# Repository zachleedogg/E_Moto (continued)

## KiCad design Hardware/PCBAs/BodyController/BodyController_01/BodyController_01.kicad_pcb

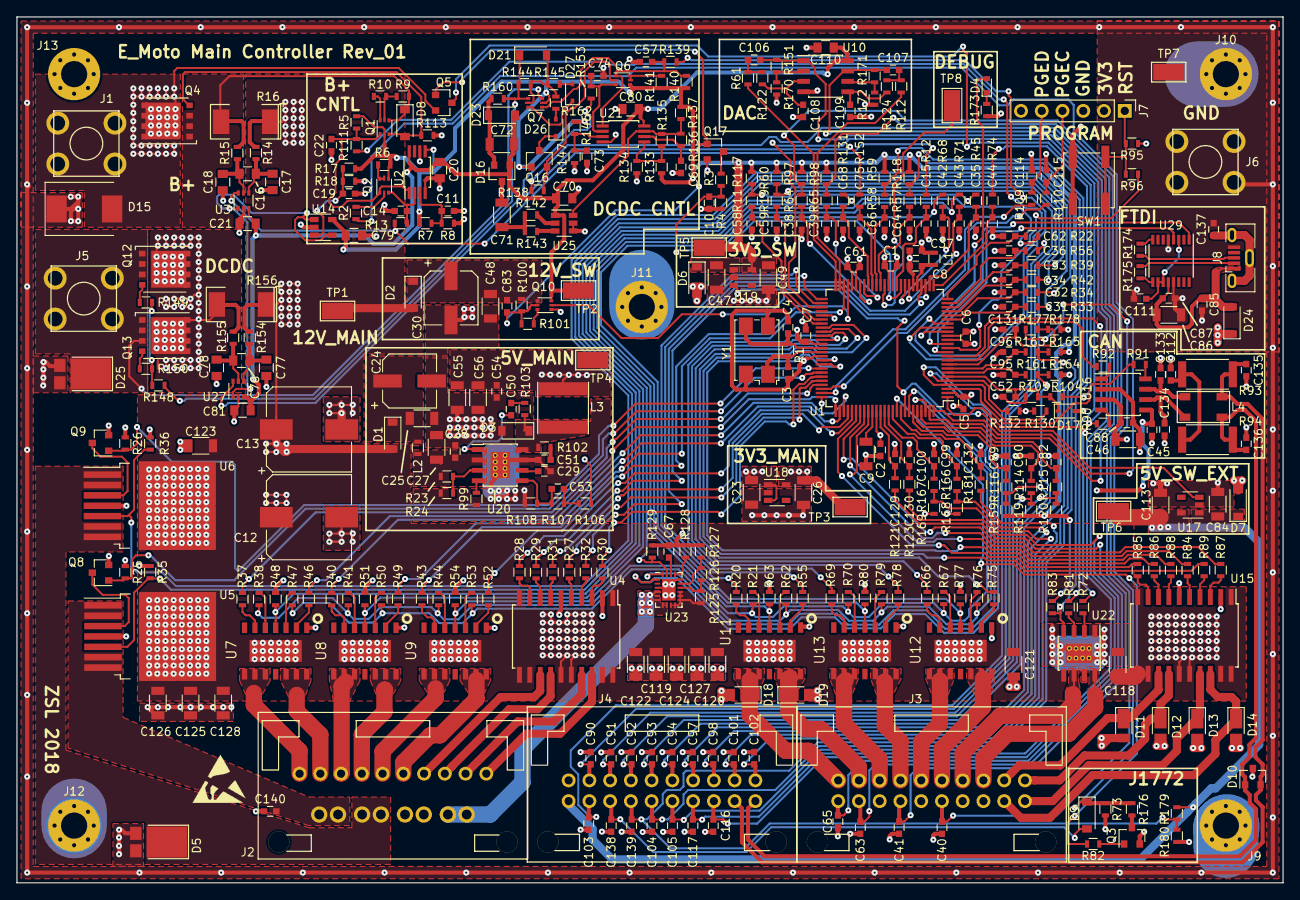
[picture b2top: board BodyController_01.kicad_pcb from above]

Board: 4 copper layers, 155.0 x 106.0 mm, 415 parts (0 on the bottom side), 284 nets.

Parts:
C1, C2, C5, C6, C7, C8, C37, C50, C61, C83, C87, C111: 100nF; C_0603
C3, C4, C53, C133, C134, C135, C136: 18pF; C_0603
C9, C26, C46, C49, C55, C56, C113, C118, C119, C120, C121, C122, C123, C124, C125, C126, C127, C128: 10uF; C_1206
C10, C11, C15, C19, C28, C29, C31, C32, C33, C34, C35, C36, C38, C39, C40, C41, C42, C43, C44, C45, C51, C52, C54, C58, C59, C60, C62, C63, C64, C65, C66, C67, C68, C73, C75, C82, C85, C88, C89, C90, C91, C92, C93, C94, C95, C96, C97, C98, C99, C100, C101, C102, C103, C104, C105, C106, C107, C108, C109, C112, C114, C115, C116, C117, C129, C130, C131, C132, C137, C138, C139, C140: 10nF; C_0603
C12, C13: 470uF; CP_Elec_10x10
C14, C22, C57, C69, C74: 1nF; C_0603
C16, C17, C18, C20, C21, C70, C76, C77, C78, C79, C80, C81, C110: 1uF; C_0805
C23, C25, C27, C47, C48, C71, C72, C84, C86: 4u7; C_1206
C24, C30: 47uF; CP_Elec_6.3x7.7
D1, D2, D3, D6, D7, D9, D24: D_Schottky; D_SOD-123
D4: D_LED; D_0603
D5, D25: D; SOT1289
D8, D21, D23: D_Zener_15V; D_SOD-123
D10: D_Schottky_x2_ACom_AKK; D_SOT-23_ANK
D11, D12, D13, D14, D18, D19: D; D_PowerDI-123
D15: D_TVS; D_SMC
D16: D_Schottky_x2_Serial_AKC; SOT-23
D17, D26, D27: D_Schottky; D_SOD-323
J1, J5, J6: 7796
J2: Conn_01x14; 34772-0140
J3, J4: Conn_02x10_Top_Bottom; 34690-0200
J7: CONN_01X06; Pin_Header_Straight_1x06_Pitch2.54mm
J8: USB_OTG; USB_Micro-B_Vertical_Molex-105133-0001
J9, J10, J11, J12, J13: Conn_01x01; MountingHole_3.2mm_M3_Pad_Via
L1, L2: Ferrite_Bead; L_0603
L3: 10uH; Inductor_Taiyo-Yuden_NR-60xx
L4: EMI_Filter_CommonMode; ACT45B
NT1, NT2, NT3, NT4: Net_Tie-0.5mm
Q1, Q2, Q6, Q7, Q10: NX1029X,115; SOT-666
Q3, Q8, Q9, Q16: 2N7002; SOT-23
Q4: SQJ423EP-T1_GE3; TDSON-8-1
Q5, Q17: Q_PMOS_GSD; SOT-23
Q12, Q13: BUK7J1R4-40HX; TDSON-8-1
R1: 1M; R_0603
R2, R20, R21, R27, R28, R30, R31, R37, R38, R40, R41, R43, R44, R46, R47, R49, R50, R52, R53, R55, R62, R66, R67, R69, R70, R72, R75, R76, R78, R79, R81, R82, R84, R85, R87, R88, R90, R91, R92, R109, R110, R138, R173: 100R; R_0603
R3, R104, R127: 34k; R_0603
R4, R35, R36, R48, R51, R54, R63, R77, R80, R83, R105, R160: 4k7; R_0603
R5, R6, R7, R10, R11, R12, R13, R17, R18, R19, R22, R29, R32, R39, R42, R45, R56, R57, R58, R64, R65, R68, R71, R74, R86, R89, R95, R96, R97, R98, R101, R113, R114, R115, R116, R121, R123, R129, R131, R137, R140, R141, R145, R146, R151, R152, R153, R161, R162, R163, R166, R167, R171, R181: 10k; R_0603
R8, R9, R25, R26, R59, R60, R100, R111, R117, R118, R119, R120, R126, R130, R132, R133, R134, R135, R136, R139, R144, R147, R159, R164, R165, R168, R169, R178: 100k; R_0603
R14, R15, R102, R103, R142, R143, R148, R149, R150, R154, R155: 3R0; R_0603
R16: R0005; SMD-2512_Pol
R23, R125, R177: 560k; R_0603
R24, R61, R108, R112, R122, R124: 150k; R_0603
R33, R34: 10K; R_0603
R73: 2k74; R_0603
R93, R94: 60R; R_2512
R99: 49k9; R_0603
R106, R174, R175: 22R; R_0603
R107: 845k; R_0603
R128, R170, R172: 22k; R_0603
R156: R0003; SMD-2512_Pol
R176: 1k3; R_0603
R179, R180: 330R; R_0603
SW1: PTS645SM43SMTR92 LFS; SW_SPST_EVQP0
TP1, TP2, TP3, TP4, TP5, TP6, TP7, TP8: TEST_1P; Test_Point_Keystone_5019_Minature
U1: PIC33EPxxxMU810; TQFP-100_14x14mm_Pitch0.5mm
U2, U21: LM2903QDRQ1; TSSOP-8_3x4.4mm_Pitch0.65mm
U3, U27: INA21x; SOT-363_SC-70-6
U4, U15: BTS716G; SOIC-20W_7.5x12.8mm_Pitch1.27mm
U5, U6: BTS500801TMAATMA1; TO-220-7Lead_TabPin8
U7, U8, U9, U11, U12, U13: BTS50202EKAXUMA2; PG_DSO_14_40_EP
U10: LM2904AVQDRQ1; SOIC-8_3.9x4.9mm_Pitch1.27mm
U14: OPA320-Q1; SOT-23-5
U16: TCAN1051GVDRQ1; SOIC-8_3.9x4.9mm_Pitch1.27mm
U17: TPS70950QDBVRQ1; SOT-23-5
U18, U19: TPS70933QDBVRQ1; SOT-23-5
U20: LMR140x0; HTSOP-8-1EP_3.9x4.9mm_Pitch1.27mm_ThermalVias
U22: DRV8872DDARQ1; HTSOP-8-1EP_3.9x4.9mm_Pitch1.27mm_ThermalVias
U23: tps25940-q1; QFN-20-1EP_3x4mm_Pitch0.5mm
U25: UCC27511A-Q1; SOT-23-6
U29: FT230X; SSOP-16_3.9x4.9mm_Pitch0.635mm
Y1: 8MHz; Crystal_SMD_7050-4pin_7.0x5.0mm

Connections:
1V65_REF: U3.1, U14.1, U14.4, U27.1
12P_MONITOR_AI: C52.1, D17.1, R104.2, R105.1, U1.6
12V_MONITOR_AI: C10.1, R3.2, R4.1, U1.34
+3.3VA: C8.1, L1.1, U1.30
+3.3VP: C49.1, C79.2, Q1.2, Q2.4, Q6.4, Q7.2, Q16.1, R5.1, R6.1, R7.1, R17.1, R59.1, R60.1, R83.1, R97.2, R98.2, R117.1, R118.1, R119.1, R120.1, R133.1, R137.1, R140.1, R141.1, R146.1, R159.1, R164.1, R165.1, TP5.1, U2.5, U14.5, U19.5
+3V3: C1.1, C2.1, C5.1, C6.1, C7.1, C26.1, C37.1, C45.1, C61.1, J7.2, L1.2, R95.1, R130.1, R132.1, R168.1, R169.1, TP3.1, U1.2, U1.16, U1.37, U1.46, U1.55, U1.62, U1.86, U16.5, U18.5
+5V: C23.1, C46.1, C54.1, C55.1, C56.1, C88.1, D24.1, L3.2, R106.1, TP4.1, U16.3, U18.1, U18.3
+5VP: C113.1, J4.11, R179.1, TP6.1, U17.5
+12P: C20.2, C21.2, C70.2, C72.2, C80.2, C81.2, C110.1, D16.1, D23.2, Q10.3, TP2.1, U2.8, U3.3, U10.8, U21.8, U25.1, U27.3
+12V: C12.1, C13.1, C118.1, C119.1, C120.1, C121.1, C122.1, C123.1, C124.1, C125.1, C126.1, C127.1, C128.1, D1.2, D2.2, D6.2, D7.2, NT2.1, NT4.1, Q17.2, R16.1, R125.2, R156.1, TP1.1, U4.1, U4.10, U4.11, U4.12, U4.15, U4.16, U4.19, U4.20, U5.4, U5.8, U6.4, U6.8, U7.TAB, U8.TAB, U9.TAB, U11.TAB, U12.TAB, U13.TAB, U15.1, U15.10, U15.11, U15.12, U15.15, U15.16, U15.19, U15.20, U22.5, U23.9, U23.10, U23.11, U23.12, U23.13
+BATT: D15.2, J1.1, Q4.5, Q5.2
/TopLevel/Communication/CAN_FILT_N: C134.2, L4.3, U16.6
/TopLevel/Communication/CAN_FILT_P: C133.2, L4.1, U16.7
/TopLevel/DCDC/ChargePump: C72.1, D16.2, D23.1, R160.1
/TopLevel/DCDC/DCDC_SHUNT: NT3.1, Q12.5, Q13.5, R156.2
/TopLevel/PowerInput/BATT_SHUNT: D8.1, NT1.1, Q1.4, Q4.1, Q4.2, Q4.3, R9.1, R16.2
/TopLevel/PowerRails/buck_bt: C50.2, U20.1
/TopLevel/PowerRails/buck_fb: C53.2, R107.2, R108.1, U20.5
/TopLevel/PowerRails/buck_freq: R99.1, U20.4
/TopLevel/PowerRails/buck_holdup: C24.1, C25.1, D1.1, L2.2
/TopLevel/PowerRails/buck_input: C27.1, C28.1, L2.1, R23.1, U20.2
/TopLevel/PowerRails/buck_ss: C29.1, U20.6
/TopLevel/PowerRails/buck_sw: D3.1, L3.1, R102.2, R103.1, U20.8
/TopLevel/PowerRails/buck_uvlo: R23.2, R24.1, U20.3
AUX_PORT_EN: Q8.1, R25.1, U1.69
AUX_PORT_ISENSE_AI: C31.1, R33.2, U1.20
AUX_PORT_OUT: C140.1, J2.11, U5.1, U5.2, U5.6, U5.7
BATTERY_CONTACTOR_EN: R84.2, U1.83
BATTERY_CONTACTOR_OUT: D13.1, J3.20, U15.17
BATT_EN: R2.2, U1.100
BATT_ISENSE_AI: C15.1, R12.2, U1.35
BATT_~FAULT: R111.2, U1.19
BMS_CONTROLLER_EN: R75.2, U1.58
BMS_CONTROLLER_OUT: J3.6, U12.12, U12.13, U12.14
BRAKE_LIGHT_EN: R37.2, U1.72
BRAKE_LIGHT_OUT: J2.1, U7.8, U7.9, U7.10
BRAKE_SWITCH_1: C104.1, J4.15, R57.1, R118.2
BRAKE_SWITCH_1_IN: C64.1, R57.2, U1.39
BRAKE_SWITCH_2: C105.1, J4.16, R58.1, R59.2
BRAKE_SWITCH_2_IN: C66.1, R58.2, U1.40
BRIGHTS_SWITCH: C92.1, J4.4, R114.1, R119.2
BRIGHTS_SWITCH_IN: C60.1, R114.2, U1.96
CAN_N: C136.2, D10.2, J4.20, L4.4, R94.1
CAN_P: C135.2, D10.3, J4.19, L4.2, R93.2
CAN_RX: R90.2, U1.11
CAN_SLEEP: R91.2, U1.3
CAN_TX: R92.2, U1.10
CHARGER_CONTACTOR_EN: R85.2, U1.81
CHARGER_CONTACTOR_OUT: D11.1, J3.9, U15.13
CHARGE_CONTROLLER_EN: R69.2, U1.61
CHARGE_CONTROLLER_OUT: J3.3, U13.8, U13.9, U13.10
CHARGE_PORT_RELEASE_EN: R81.2, U1.53
CHARGE_PORT_RELEASE_OUT: J3.8, U22.8
CONTACT_1_2_STATUS: R89.2, U1.66
CONTACT_3_4_STATUS: R86.2, U1.67
DAC_OUT_1: C106.1, C117.1, J4.17, R151.2, U10.1
DAC_OUT_2: C107.1, C116.1, J4.18, R171.2, U10.7
DAC_PWM_1: R61.1, U1.50
DAC_PWM_2: R112.1, U1.49
DCDC: D25.1, J5.1, Q7.3, Q12.1, Q12.2, Q12.3, Q13.1, Q13.2, Q13.3
DCDC_CONTACTOR_EN: R87.2, U1.82
DCDC_CONTACTOR_OUT: D14.1, J3.19, U15.18
DCDC_EN: R138.2, U1.99
DCDC_ISENSE_AI: C75.1, R152.2, U1.41
DCDC_~FAULT: R139.2, U1.18
DEBUG_LED: D4.2, U1.17
DEBUG_PIN: TP8.1, U1.38
DIAG_EN: R47.2, R50.2, R53.2, R62.2, R76.2, R79.2, U1.94
DIAG_SELECT: R21.2, R38.2, R41.2, R44.2, R67.2, R70.2, U1.98
DIVIDER_EN: C83.2, Q5.1, Q10.5, Q17.1, R100.2, R101.1
ECU_1_ISENSE_AI: C42.1, R68.2, U1.33
ECU_2_ISENSE_AI: C43.1, R71.2, U1.32
FAN_1_EN: R55.2, U1.51
FAN_1_OUT: D19.1, J3.2, U11.12, U11.13, U11.14
FAN_ISENSE_AI: C62.1, R22.2, U1.25
FAN_SPEED_1_OUT: C63.1, J3.12, R121.1
FAN_SPEED_1_PWM: C129.1, R121.2, U1.87
GND: C1.2, C2.2, C3.2, C4.2, C5.2, C6.2, C7.2, C8.2, C9.2, C10.2, C11.2, C12.2, C13.2, C14.1, C15.2, C17.2, C18.2, C19.2, C20.1, C21.1, C22.1, C23.2, C24.2, C25.2, C26.2, C27.2, C28.2, C29.2, C30.2, C31.2, C32.2, C33.2, C34.2, C35.2, C36.2, C37.2, C38.2, C39.2, C40.2, C41.2, C42.2, C43.2, C44.2, C45.2, C46.2, C47.2, C48.2, C49.2, C51.1, C52.2, C54.2, C55.2, C56.2, C57.1, C58.2, C59.2, C60.2, C61.2, C62.2, C63.2, C64.2, C65.2, C66.2, C67.2, C68.2, C69.2, C70.1, C73.2, C74.1, C75.2, C77.2, C78.2, C79.1, C80.1, C81.1, C82.2, C84.2, C85.2, C86.2, C87.2, C88.2, C89.2, C90.2, C91.2, C92.2, C93.2, C94.2, C95.2, C96.2, C97.2, C98.2, C99.2, C100.2, C101.2, C102.2, C103.2, C104.2, C105.2, C108.2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
HEADLIGHT_HI_EN: R49.2, U1.77
HEADLIGHT_HI_OUT: J2.4, U8.12, U8.13, U8.14
HEADLIGHT_ISENSE_AI: C34.1, R42.2, U1.22
HEADLIGHT_LO_EN: R40.2, U1.78
HEADLIGHT_LO_OUT: J2.3, U8.8, U8.9, U8.10
HEATED_GRIPS_EN: R52.2, U1.47
HEATED_GRIPS_OUT: J2.6, U9.12, U9.13, U9.14
HEATED_SEAT_EN: R43.2, U1.48
HEATED_SEAT_OUT: J2.5, U9.8, U9.9, U9.10
HEATER_ISENSE_AI: C35.1, R45.2, U1.27
HORN_EN: Q9.1, R26.1, U1.68
HORN_ISENSE_AI: C32.1, R34.2, U1.21
HORN_OUT: D5.1, J2.12, U6.1, U6.2, U6.6, U6.7
HORN_SWITCH: C93.1, J4.5, R115.1, R120.2
HORN_SWITCH_IN: C82.1, R115.2, U1.97
IC_CONTROLLER_ISENSE_AI: C68.1, R131.2, U1.42
IC_CONTROLLER_OUT: J2.14, U23.4, U23.5, U23.6, U23.7, U23.8
IC_CONTROLLER_SLEEP: R130.2, U1.4, U23.1
IC_CONTROLLER_~FLT: R132.2, U1.5, U23.20
IGNITION_SWITCH_IN: C99.1, R166.2, U1.90
INGITION_SWITCH: C101.1, J4.9, R166.1, R168.2
J1772_CONTROLLER_EN: R66.2, U1.59
J1772_CONTROLLER_OUT: J3.5, U12.8, U12.9, U12.10
KICKSTAND_SWITCH: C94.1, J4.6, R116.1, R159.2
KICKSTAND_SWITCH_IN: C89.1, R116.2, U1.95
KILL_SWITCH: C102.1, J4.10, R167.1, R169.2
KILL_SWITCH_IN: C100.1, R167.2, U1.89
LOCK_ISENSE_AI: C44.1, R74.2, U1.26
MOTOR_CONTROLLER_EN: R78.2, U1.60
MOTOR_CONTROLLER_OUT: J3.4, U13.12, U13.13, U13.14
unnamed: C3.1, R1.1, U1.64, Y1.1
unnamed: C4.1, R1.2, U1.63, Y1.3
unnamed: C9.1, U1.85
unnamed: C11.1, R7.2, R8.1, U2.3
unnamed: C14.2, Q2.3, R13.2, U2.2
unnamed: C16.1, C18.1, R15.2, U3.5
unnamed: C16.2, C17.1, R14.2, U3.4
unnamed: C19.1, R17.2, R18.1, U14.3
unnamed: C22.2, Q1.1, Q2.1, R5.2, R111.1, U2.1
unnamed: C30.1, C48.1, C83.1, D2.1, Q10.4, R100.1
unnamed: C47.1, D6.1, U19.1
unnamed: C50.1, R103.2
unnamed: C51.2, R102.1
unnamed: C53.1, R106.2, R107.1
unnamed: C57.2, Q6.1, Q7.1, R139.1, R140.2, U21.1
unnamed: C67.1, U23.18
unnamed: C69.1, R136.2, U21.6
unnamed: C71.1, D16.3
unnamed: C71.2, R142.1, R143.1
unnamed: C73.1, R146.2, R147.1, U21.3
unnamed: C74.2, Q6.3, R153.2, U21.2
unnamed: C76.1, C78.1, R155.2, U27.5
unnamed: C76.2, C77.1, R154.2, U27.4
unnamed: C84.1, D7.1, U17.1
unnamed: C106.2, R61.2, R122.1
unnamed: C107.2, R112.2, R124.1
unnamed: C108.1, R122.2, U10.3
unnamed: C109.1, R124.2, U10.5
unnamed: C111.1, U29.3, U29.10, U29.11
unnamed: C112.1, R93.1, R94.2
unnamed: C114.1, J7.5, R109.1
unnamed: C115.1, J7.4, R110.1
unnamed: C137.1, J8.6
unnamed: D4.1, R173.2
unnamed: D8.2, Q1.3, Q4.4, R113.1
unnamed: D9.1, R73.1, R176.1, R177.1
unnamed: D21.1, Q7.4, R144.1, R148.1, R160.2
unnamed: D21.2, Q7.5, R144.2, R145.1, R162.1
unnamed: D26.1, Q16.3
unnamed: D26.2, R162.2
unnamed: D27.1, Q7.6
unnamed: D27.2, R145.2
unnamed: NT1.2, R15.1
unnamed: NT2.2, R14.1
unnamed: NT3.2, R155.1
unnamed: NT4.2, R154.1
unnamed: Q1.5, R9.2, R10.1
unnamed: Q1.6, R10.2
unnamed: Q2.2, R2.1
unnamed: Q2.5, Q2.6, R6.2
unnamed: Q3.1, R82.1
unnamed: Q3.3, R176.2
unnamed: Q5.3, R104.1
unnamed: Q6.5, Q6.6, R141.2
unnamed: Q8.3, U5.3
unnamed: Q9.3, U6.3
unnamed: Q10.6, R101.2
unnamed: Q12.4, R149.2
unnamed: Q13.4, R150.2
unnamed: Q6.2, Q16.2, R138.1
unnamed: Q17.3, R3.1
unnamed: R12.1, R13.1, U3.6
unnamed: R20.1, U11.6
unnamed: R21.1, U11.5
unnamed: R22.1, R63.2, U11.4
unnamed: R27.1, U4.5
unnamed: R28.1, U4.9
unnamed: R29.1, U4.8
unnamed: R30.1, U4.3
unnamed: R31.1, U4.7
unnamed: R32.1, U4.4
unnamed: R33.1, R35.2, U5.5
unnamed: R34.1, R36.2, U6.5
unnamed: R37.1, U7.6
unnamed: R38.1, U7.5
unnamed: R39.1, R48.2, U7.4
unnamed: R40.1, U8.6
unnamed: R41.1, U8.5
unnamed: R42.1, R51.2, U8.4
unnamed: R43.1, U9.6
unnamed: R44.1, U9.5
unnamed: R45.1, R54.2, U9.4
unnamed: R46.1, U7.2
unnamed: R47.1, U7.3
unnamed: R49.1, U8.2
unnamed: R50.1, U8.3
unnamed: R52.1, U9.2
unnamed: R53.1, U9.3
unnamed: R55.1, U11.2
unnamed: R62.1, U11.3
unnamed: R66.1, U12.6
unnamed: R67.1, U12.5
unnamed: R68.1, R77.2, U12.4
unnamed: R69.1, U13.6
unnamed: R70.1, U13.5
unnamed: R71.1, R80.2, U13.4
unnamed: R72.1, U22.2
unnamed: R74.1, R83.2, U22.4
unnamed: R75.1, U12.2
unnamed: R76.1, U12.3
unnamed: R78.1, U13.2
unnamed: R79.1, U13.3
unnamed: R81.1, U22.3
unnamed: R84.1, U15.5
unnamed: R85.1, U15.9
unnamed: R86.1, U15.8
unnamed: R87.1, U15.3
unnamed: R88.1, U15.7
unnamed: R89.1, U15.4
unnamed: R90.1, U16.4
unnamed: R91.1, U16.8
unnamed: R92.1, U16.1
unnamed: R96.1, U1.13
unnamed: R125.1, R126.2, U23.14
unnamed: R126.1, R127.2, U23.15
unnamed: R128.2, U23.17
unnamed: R129.2, R131.1, U23.19
unnamed: R133.2, R134.1, R135.2, U21.5
unnamed: R135.1, R136.1, R137.2, U21.7, U25.6
unnamed: R142.2, U25.2
unnamed: R143.2, U25.3
unnamed: R148.2, R149.1, R150.1
unnamed: R151.1, R170.2, U10.2
unnamed: R152.1, R153.1, U27.6
unnamed: R171.1, R172.2, U10.6
unnamed: R174.2, U29.8
unnamed: R175.2, U29.9
PGEC: R109.2, U1.74
PGED: R110.2, U1.73
PILOT: C138.1, D9.2, J4.13
PILOT_EN: R82.2, U1.91
PILOT_MONITOR_AI: C131.1, R177.2, R178.1, U1.9
PRECHARGE_RELAY_EN: R88.2, U1.84
PRECHARGE_RELAY_OUT: D12.1, J3.10, U15.14
PROXIMITY: C139.1, J4.14, R179.2, R180.1, R181.2
PROXIMITY_MONITOR_AI: C132.1, R181.1, U1.92
PUMP_1_EN: R20.2, U1.52
PUMP_1_OUT: D18.1, J3.1, U11.8, U11.9, U11.10
PUMP_SPEED_1_OUT: C65.1, J3.11, R123.1
PUMP_SPEED_1_PWM: C130.1, R123.2, U1.88
RADIATOR_INPUT_TEMP_AI: C39.1, R65.2, U1.43
RADIATOR_INPUT_TEMP_OUT: C41.1, J3.14, R65.1, R98.1
RADIATOR_OUTPUT_TEMP_AI: C38.1, R64.2, U1.44
RADIATOR_OUTPUT_TEMP_OUT: C40.1, J3.16, R64.1, R97.1
SPARE_SWITCH_1: C97.1, J4.7, R161.1, R164.2
SPARE_SWITCH_1_IN: C95.1, R161.2, U1.7
SPARE_SWITCH_2: C98.1, J4.8, R163.1, R165.2
SPARE_SWITCH_2_IN: C96.1, R163.2, U1.8
STEERING_COLUMN_LOCK_EN: R72.2, U1.1
STEERING_COLUMN_LOCK_OUT: J3.7, U22.6
SW_EN: Q10.2, U1.93, U17.3, U19.3
TAILLIGHT_EN: R46.2, U1.76
TAILLIGHT_ISENSE_AI: C33.1, R39.2, U1.23
TAILLIGHT_OUT: J2.2, U7.12, U7.13, U7.14
THROTTLE_SIGNAL: C103.1, J4.12, R56.1
THROTTLE_SIGNAL_MONITOR_AI: C36.1, R56.2, U1.24
TURN_LEFT_SWITCH: C90.1, J4.2, R11.1, R117.2
TURN_LEFT_SWITCH_IN: C58.1, R11.2, U1.57
TURN_RIGHT_SWITCH: C91.1, J4.3, R19.1, R60.2
TURN_RIGHT_SWITCH_IN: C59.1, R19.2, U1.56
TURN_SGINAL_FL_EN: R31.2, U1.79
TURN_SIGNAL_FL_OUT: J2.8, U4.14
TURN_SIGNAL_FR_EN: R30.2, U1.70
TURN_SIGNAL_FR_OUT: J2.10, U4.18
TURN_SIGNAL_L_STATUS: R29.2, U1.29
TURN_SIGNAL_RL_EN: R28.2, U1.80
TURN_SIGNAL_RL_OUT: J2.7, U4.13
TURN_SIGNAL_RR_EN: R27.2, U1.71
TURN_SIGNAL_RR_OUT: J2.9, U4.17
TURN_SIGNAL_R_STATUS: R32.2, U1.28
UART_RX: U1.14, U29.1
UART_TX: U1.12, U29.4
USB_5V: C85.1, C86.1, C87.1, D24.2, J8.1, U29.12
USB_D+: J8.3, R174.1
USB_D-: J8.2, R175.1
~RESET: J7.1, R95.2, R96.2, SW1.2

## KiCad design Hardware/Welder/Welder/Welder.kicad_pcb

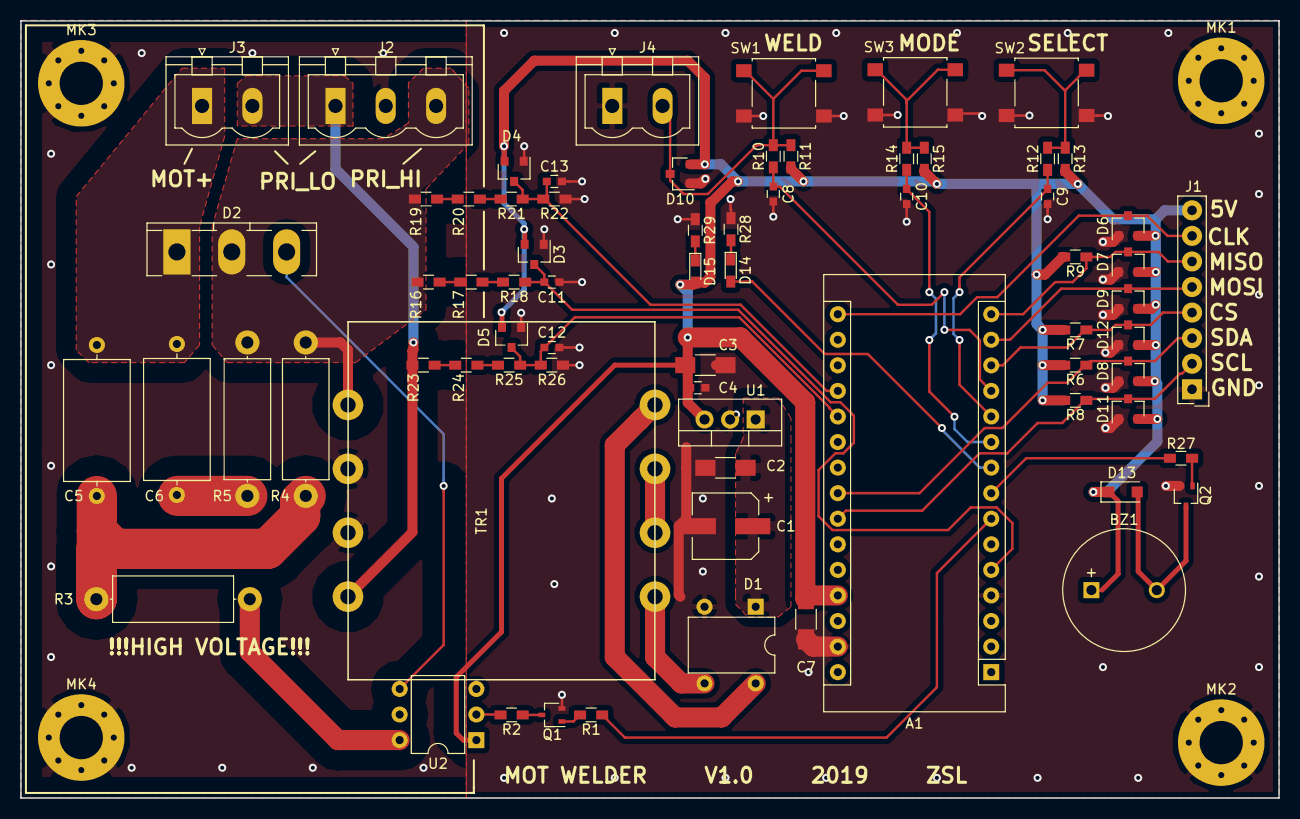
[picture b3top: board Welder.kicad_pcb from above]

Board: 2 copper layers, 125.0 x 77.2 mm, 75 parts (0 on the bottom side), 44 nets.

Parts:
A1: Arduino_Nano_v3.x; Arduino_Nano
BZ1: Buzzer; MagneticBuzzer_ProSignal_ABT-410-RC
C1: 47u; CP_Elec_6.3x7.7
C2, C3, C7: 10uF; C_1206_HandSoldering
C4, C8, C9, C10, C11, C12, C13: 10nF; C_0603
C5: 0.047uF; C_Axial_L12.0mm_D6.5mm_P15.00mm_Horizontal
C6: 0.1uF; C_Axial_L12.0mm_D6.5mm_P15.00mm_Horizontal
D1: D_Bridge_+-AA; Diode_Bridge_DIP-4_W7.62mm_P5.08mm
D2: Q_TRIAC_A1A2G; TO-280_Vertical
D3, D4, D5, D6, D7, D8, D9, D10, D11, D12: D_Schottky_x2_Serial_AKC; SOT-23
D13: D; D_SOD-123F
D14, D15: LED; LED_0603_HandSoldering
J1: Conn_01x08; SL-108-X-XX_1x08
J2: Screw_Terminal_01x03; PhoenixContact_MSTBVA-G_03x5.00mm_Vertical
J3, J4: Screw_Terminal_01x02; PhoenixContact_MSTBVA-G_02x5.00mm_Vertical
MK1, MK2, MK3, MK4: Mounting_Hole_PAD; MountingHole_4.3mm_M4_Pad_Via
Q1, Q2: Q_NMOS_GSD; SOT-323_SC-70
R1, R6, R7, R8, R9, R10, R11, R12, R13, R14, R15, R27: 10k; R_0603_HandSoldering
R2: 220R; R_0603_HandSoldering
R3: 360R; R_Axial_DIN0414_L11.9mm_D4.5mm_P15.24mm_Horizontal
R4: 470R; R_Axial_DIN0414_L11.9mm_D4.5mm_P15.24mm_Horizontal
R5: 39R; R_Axial_DIN0414_L11.9mm_D4.5mm_P15.24mm_Horizontal
R16, R17, R18, R19, R20, R21, R23, R24, R25: 165k; R_0603_HandSoldering
R22, R26: 14k7; R_0603_HandSoldering
R28, R29: 360R; R_0603_HandSoldering
SW1, SW2, SW3: SW_Push; SW_SPST_B3S-1000
TR1: TRANSF6; FS20-120-C2
U1: LM7805_TO220; TO-220-3_Vertical
U2: MOC3052M; DIP-6_W7.62mm

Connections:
+5V: A1.27, BZ1.1, C3.1, C4.1, C7.1, D3.2, D4.2, D5.2, D6.2, D7.2, D8.2, D9.2, D10.2, D11.2, D12.2, D13.1, D15.2, J1.8, R6.2, R7.2, R8.2, R9.2, R11.2, R13.2, R15.2, U1.3, U2.1
BUZZ_PWM: A1.8, R27.1
CLK: A1.16, D6.3, J1.7
CS: A1.13, D12.3, J1.4, R7.1
DEBUG_LED_EN: A1.9, D14.2
GND: A1.4, A1.29, C1.2, C2.2, C3.2, C4.2, C7.2, C8.2, C9.2, C10.2, C11.2, C12.2, C13.2, D1.2, D3.1, D4.1, D5.1, D6.1, D7.1, D8.1, D9.1, D10.1, D11.1, D12.1, J1.1, J2.2, J4.1, MK1.1, MK2.1, MK3.1, MK4.1, Q1.2, Q2.2, R22.1, R26.1, R28.1, R29.1, SW1.2, SW2.2, SW3.2, TR1.2, TR1.3, U1.2
MISO: A1.15, D7.3, J1.6, R9.1
MODE_BUTTON: A1.10, C10.1, R14.1
MOSI: A1.14, D9.3, J1.5
MOT_+: C5.2, C6.2, D2.1, J3.1
MOT_EN: A1.7, R1.1
unnamed: BZ1.2, D13.2, Q2.3
unnamed: C1.1, C2.1, D1.1, U1.1
unnamed: C5.1, R3.1, R4.2
unnamed: C6.1, R5.2
unnamed: D1.3, TR1.8
unnamed: D1.4, TR1.5
unnamed: D2.3, U2.4
unnamed: D14.1, R28.2
unnamed: D15.1, R29.2
unnamed: Q1.1, R1.2
unnamed: Q1.3, R2.1
unnamed: Q2.1, R27.2
unnamed: R2.2, U2.2
unnamed: R3.2, U2.6
unnamed: R12.2, R13.1, SW2.1
unnamed: R14.2, R15.1, SW3.1
unnamed: R16.1, R17.2
unnamed: R17.1, R18.2
unnamed: R19.1, R20.2
unnamed: R20.1, R21.2
unnamed: R23.1, R24.2
unnamed: R24.1, R25.2
unnamed: TR1.6, TR1.7
PRIMARY_A_AI: A1.19, C13.1, D4.3, R21.1, R22.2
PRIMARY_B_AI: A1.20, C12.1, D5.3, R25.1, R26.2
PRI_HI: D2.2, J2.3, R4.1, R5.1, R16.2, R19.2, TR1.1
PRI_LO: J2.1, J3.2, R23.2, TR1.4
SCL: A1.24, D11.3, J1.2, R8.1
SDA: A1.23, D8.3, J1.3, R6.1
SELECT_BUTTON: A1.11, C9.1, R12.1
WELD_BUTTON: A1.12, C8.1, R10.1
WELD_BUTTON_OUT: D10.3, J4.2, R10.2, R11.1, SW1.1
ZERO_CROSS: A1.5, C11.1, D3.3, R18.1

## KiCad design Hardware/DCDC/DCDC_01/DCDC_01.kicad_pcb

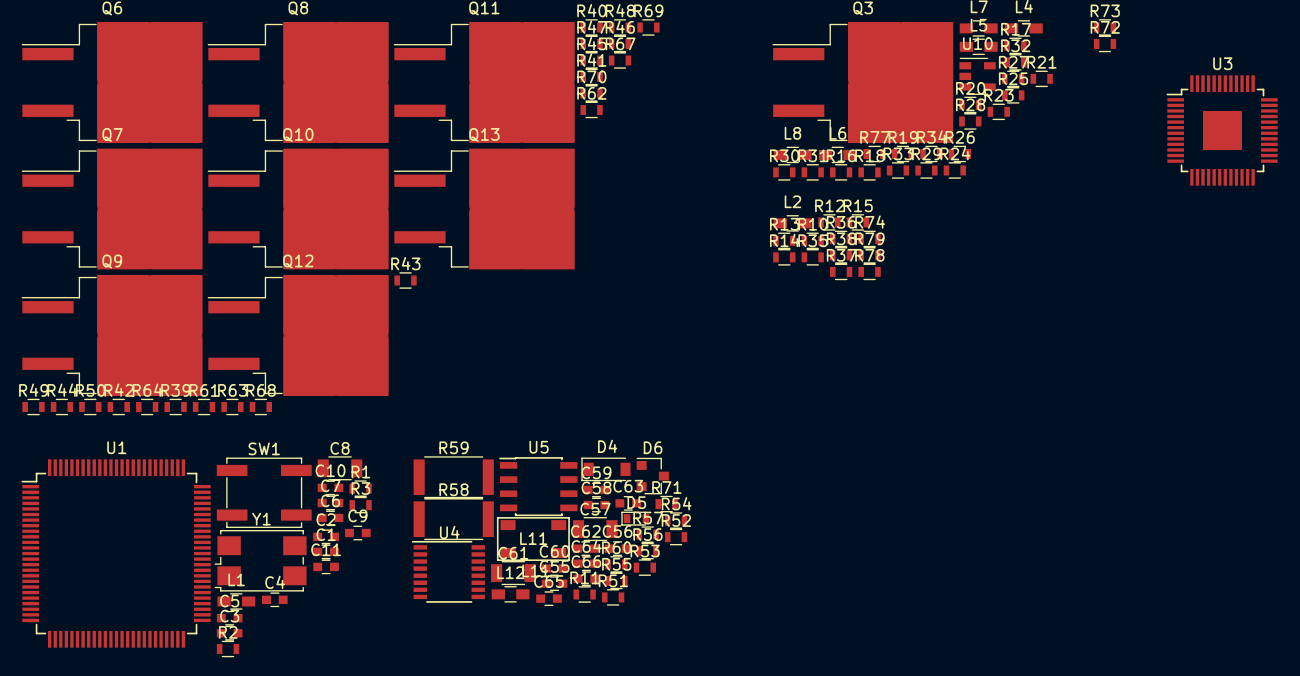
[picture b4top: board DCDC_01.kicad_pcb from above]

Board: 2 copper layers, 119 parts (0 on the bottom side), 83 nets, no tracks yet.

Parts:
C1, C2, C3, C4, C5, C6, C7, C9, C55, C58: 100nF; C_0603
C8, C61: 10uF; C_1206
C10, C11, C62, C63, C64, C65: 18pF; C_0603
C56, C59, C60, C66: 10nF; C_0603
C57: 4u7; C_1206
D4: D_Schottky; D_SOD-123
D5: D_LED; D_0603
D6: D_Schottky_x2_ACom_AKK; D_SOT-23_ANK
L1, L2, L4, L5, L6, L7, L8, L12: Ferrite_Bead; L_0603_HandSoldering
L11: EMI_Filter_CommonMode; ACT45B
Q3, Q6, Q7, Q8, Q9, Q10, Q11, Q12, Q13: Q_NMOS_GDS; TO-263-2
R1, R2, R14, R34, R36, R37, R47, R48, R78: 10k; R_0603
R3: 1M; R_0603
R10, R49, R50, R61, R62, R63, R64, R67, R68, R69, R70: 3R3; R_0603
R11, R15, R24, R38, R53, R54, R55, R56, R60, R72, R73, R74, R79: 100R; R_0603
R12, R16, R33, R35: 100k; R_0603
R13: 47k; R_0603
R17, R18, R19, R20, R21, R25, R26, R27, R28, R29, R30, R31, R39, R40, R41, R42, R43, R44, R45, R46: 0R0; R_0603
R23: 3k83; R_0603
R32: 20R; R_0603
R51, R52: 22R; R_0603
R57, R71: 2k2; R_0603
R58, R59: 60R; R_2512
R77: 22k; R_0603
SW1: PTS645SM43SMTR92 LFS; SW_SPST_EVQP0
U1: PIC33EPxxxMU810; TQFP-100_14x14mm_Pitch0.5mm
U3: LTC7810; TQFP-48-1EP_7x7mm_Pitch0.5mm
U4: FT230X; SSOP-16_3.9x4.9mm_Pitch0.635mm
U5: TCAN1051GVDRQ1; SOIC-8_3.9x4.9mm_Pitch1.27mm
U10: OPA320-Q1; SOT-23-5
Y1: 8MHz; Crystal_SMD_7050-4pin_7.0x5.0mm

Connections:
5V_MONITOR_AI: R36.2, R37.1, U1.6
12V_MONITOR_AI: R13.2, R14.1, U1.34
+3.3VA: C7.1, L1.1, U1.30
+3V3: C1.1, C2.1, C3.1, C4.1, C5.1, C6.1, C9.1, C59.1, L1.2, R1.1, R57.1, R71.1, U1.2, U1.16, U1.37, U1.46, U1.55, U1.62, U1.86, U5.5
+5V: C60.1, C61.1, D4.1, R35.1, U5.3
+12V: L7.1, R12.1, R32.1
+BATT: L2.2, L4.2, L5.2, L6.1, L8.2
/Top_Level/Communication/CAN_FILT_N: C63.1, L11.3, U5.6
/Top_Level/Communication/CAN_FILT_P: C62.2, L11.1, U5.7
/Top_Level/Communication/USB_VCCio: C55.1, U4.3, U4.10, U4.11
/Top_Level/DCDC_Controller/Bgate_P1: R20.1, U3.37
/Top_Level/DCDC_Controller/Bgate_P2: R27.2, U3.24
/Top_Level/DCDC_Controller/EXTVcc: L7.2, U3.11
/Top_Level/DCDC_Controller/FeedBack: R33.2, R34.1, R77.2, U3.47
/Top_Level/DCDC_Controller/INTVcc: R18.1, R28.1, R31.1, U3.3, U3.14, U3.29
/Top_Level/DCDC_Controller/NDRV: R24.2, R29.2, U3.10
/Top_Level/DCDC_Controller/Tgate_P1: R19.1, U3.42
/Top_Level/DCDC_Controller/Tgate_P2: R26.2, U3.19
/Top_Level/DCDC_Controller/VBATT_FILT_NDRV: L8.1, Q3.2
/Top_Level/DCDC_Controller/Vin: L6.2, U3.35
Bgate_P1_Res: R20.2, R40.2, R44.2
Bgate_P2_Res: R27.1, R42.2, R46.2
CAN_N: C65.1, D6.2, L11.4, R59.1
CAN_P: C64.2, D6.3, L11.2, R58.2
CAN_RX: R55.1, U1.11
CAN_SLEEP: R56.1, U1.3
CAN_TX: R54.1, U1.10
DEBUG_LED: D5.2, U1.17
DRVcc: Q3.3, R29.1, U3.26
GND: C1.2, C2.2, C3.2, C4.2, C5.2, C6.2, C7.2, C8.2, C9.2, C10.2, C11.2, C55.2, C56.2, C57.2, C58.2, C59.2, C60.2, C61.2, C62.1, C63.2, C64.1, C65.2, C66.2, D6.1, Q7.3, Q9.3, Q11.3, Q13.3, R10.2, R14.2, R16.2, R17.2, R25.2, R30.2, R34.2, R37.2, R49.2, R50.2, R60.1, SW1.1, U1.15, U1.31, U1.36, U1.45, U1.65, U1.75, U3.5, U3.25, U3.49, U4.5, U4.13, U5.2, U10.2, Y1.2, Y1.4
I2C_SCL: R57.2, U1.50
I2C_SDA: R71.2, U1.49
unnamed: C8.1, U1.85
unnamed: C10.1, R3.1, U1.64, Y1.1
unnamed: C11.1, R3.2, U1.63, Y1.3
unnamed: R16.1, U3.7
unnamed: R23.1, U3.46
unnamed: Q3.1, R24.1
unnamed: R32.2, R33.1
unnamed: C57.1, C58.1, D4.2, L12.1, U4.12
unnamed: C66.1, R58.1, R59.2
unnamed: D5.1, R60.2
unnamed: R12.2, R78.1
unnamed: Q6.1, R39.1
unnamed: Q7.1, R40.1
unnamed: Q8.1, R41.1
unnamed: Q9.1, R42.1
unnamed: Q10.1, R43.1
unnamed: Q11.1, R44.1
unnamed: Q12.1, R45.1
unnamed: Q13.1, R46.1
unnamed: R2.1, U1.13
unnamed: R11.1, U4.4
unnamed: R17.1, R18.2, U3.4
unnamed: R21.1, U3.32
unnamed: R25.1, R28.2, U3.8
unnamed: R30.1, R31.2, U3.2
unnamed: R51.2, U4.8
unnamed: R52.2, U4.9
unnamed: R53.1, U4.1
unnamed: R54.2, U5.1
unnamed: R55.2, U5.4
unnamed: R56.2, U5.8
unnamed: R77.1, U10.1, U10.4
PGEC: R72.2, U1.74
PGED: R73.2, U1.73
Phase1_Isense_AI: R47.1, U1.32
Phase2_Isense_AI: R48.1, U1.33
RUN_LTC: R21.2, U1.98
SW_EN: R15.1, R38.1, R74.1, U1.93
SW_Node_P1: Q6.3, Q7.2, Q10.3, Q11.2, U3.41
SW_Node_P2: Q8.3, Q9.2, Q12.3, Q13.2, U3.20
Sense_P1_N: R68.2, U3.1
Sense_P1_P: R62.2, U3.48
Sense_P2_N: R70.2, U3.12
Sense_P2_P: R64.2, U3.13
Tgate_P1_Res: R19.2, R39.2, R43.2
Tgate_P2_Res: R26.1, R41.2, R45.2
UART_RX: R53.2, U1.14
UART_TX: R11.2, U1.12
USB_5V: C56.1, L12.2
VBATT_FILT: L4.1, L5.1, Q6.2, Q8.2, Q10.2, Q12.2
nRESET: R1.2, R2.2, SW1.2

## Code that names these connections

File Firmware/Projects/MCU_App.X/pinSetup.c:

/* 
 * File:   pinSetup.c
 * Author: Zach Levenberg
 * Comments: Pin setup for projects
 * Revision history: 3/1/18 initial build
 */

// *****************************************************************************
// *****************************************************************************
// Section: Included Files 
// *****************************************************************************
// *****************************************************************************
#include "pinSetup.h"
#include "bolt_ADC.h"
#include "bolt_uart.h"
#include "bolt_CAN.h"
#include "pins.h"
#include "bolt_OC.h"
#include "bolt_pps.h"
#include "mcc_generated_files/clock.h"
#include "bolt_sleep.h"
#include <xc.h>

// *****************************************************************************
// *****************************************************************************
// Section: Module Defines and variables
// *****************************************************************************
// *****************************************************************************


// *****************************************************************************
// *****************************************************************************
// Section: Function Declarations
// *****************************************************************************
// *****************************************************************************

/**
 * 
 */
void PinSetup_Init(void) {
    /* Configure all AD pins as digital */
#ifdef ANSELA
    ANSELA = 0x0000;
#endif
#ifdef ANSELB
    ANSELB = 0x0000;
#endif
#ifdef ANSELC
    ANSELC = 0x0000;
#endif
#ifdef ANSELD
    ANSELD = 0x0000;
#endif
#ifdef ANSELE
    ANSELE = 0x0000;
#endif
#ifdef ANSELF
    ANSELF = 0x0000;
#endif
#ifdef ANSELG
    ANSELG = 0x0000;
#endif


    /* Set the PWM's off */
#ifdef IOCON1
    IOCON1bits.PENH = 0;
    IOCON1bits.PENL = 0;
#endif
#ifdef IOCON2
    IOCON2bits.PENH = 0;
    IOCON2bits.PENL = 0;
#endif
#ifdef IOCON3
    IOCON3bits.PENH = 0;
    IOCON3bits.PENL = 0;
#endif

    /*Set all digital IO*/
    PINS_direction(DEBUG_LED_EN, OUTPUT);
    PINS_direction(DEBUG_PIN_EN, OUTPUT);
    PINS_direction(BMS_CONTROLLER_EN, OUTPUT);
    PINS_direction(J1772_CONTROLLER_EN, OUTPUT);
    PINS_direction(MOTOR_CONTROLLER_EN, OUTPUT);
    PINS_direction(CHARGE_CONTROLLER_EN, OUTPUT);
    PINS_direction(PILOT_EN, OUTPUT);
    PINS_direction(TURN_SIGNAL_L_STATUS, INPUT);
    PINS_direction(TURN_SIGNAL_R_STATUS, INPUT);
    PINS_direction(CONTACT_1_2_STATUS, INPUT);
    PINS_direction(CONTACT_3_4_STATUS, INPUT);
    PINS_direction(SPARE_SWITCH_1_IN, INPUT);
    PINS_direction(SPARE_SWITCH_2_IN, INPUT);
    PINS_direction(BRAKE_LIGHT_EN, OUTPUT);
    PINS_direction(TAILLIGHT_EN, OUTPUT);
    PINS_direction(HEADLIGHT_HI_EN, OUTPUT);
    PINS_direction(HEADLIGHT_LO_EN, OUTPUT);
    PINS_direction(CHARGER_CONTACTOR_EN, OUTPUT);
    PINS_direction(DCDC_CONTACTOR_EN, OUTPUT);
    PINS_direction(BATTERY_CONTACTOR_EN, OUTPUT);
    PINS_direction(PRECHARGE_RELAY_EN, OUTPUT);
    PINS_direction(HORN_EN, OUTPUT);
    PINS_direction(AUX_PORT_EN, OUTPUT);
    PINS_direction(TURN_SIGNAL_FR_EN, OUTPUT);
    PINS_direction(TURN_SIGNAL_RR_EN, OUTPUT);
    PINS_direction(TURN_SIGNAL_FL_EN, OUTPUT);
    PINS_direction(TURN_SIGNAL_RL_EN, OUTPUT);
    PINS_direction(HEATED_GRIPS_EN, OUTPUT);
    PINS_direction(HEATED_SEAT_EN, OUTPUT);
    PINS_direction(SW_EN, OUTPUT);
    PINS_direction(DIAG_EN, OUTPUT);
    PINS_direction(DIAG_SELECT_EN, OUTPUT);
    PINS_direction(DCDC_EN, OUTPUT);
    PINS_direction(BATT_EN, OUTPUT);
    PINS_direction(CAN_SLEEP_EN, OUTPUT);
    PINS_direction(IC_CONTROLLER_SLEEP_EN, OUTPUT);
    PINS_direction(IC_CONTROLLER_nFAULT, INPUT);
    PINS_direction(DCDC_nFAULT, INPUT);
    PINS_direction(BATT_nFAULT, INPUT);
    PINS_direction(PUMP_1_EN, OUTPUT);
    PINS_direction(FAN_1_EN, OUTPUT);
    PINS_direction(BRAKE_SWITCH_1_IN, INPUT);
    PINS_direction(BRAKE_SWITCH_2_IN, INPUT);
    PINS_direction(IGNITION_SWITCH_IN, INPUT);
    PINS_direction(KILL_SWITCH_IN, INPUT);
    PINS_direction(TURN_LEFT_SWITCH_IN, INPUT);
    PINS_direction(TURN_RIGHT_SWITCH_IN, INPUT);
    PINS_direction(BRIGHTS_SWITCH_IN, INPUT);
    PINS_direction(HORN_SWITCH_IN, INPUT);
    PINS_direction(KICKSTAND_SWITCH_IN, INPUT);

    /*ANALOG*/
    ADC_Init();
    ADC_SetPin(FAN_ISENSE_AI);
    ADC_SetPin(THOTTLE_SIGNAL_MONITOR_AI);
    ADC_SetPin(TAILLIGHT_ISENSE_AI);
    ADC_SetPin(HEADLIGHT_ISENSE_AI);
    ADC_SetPin(HORN_ISENSE_AI);
    ADC_SetPin(AUX_PORT_ISENSE_AI);
    ADC_SetPin(LOCK_ISENSE_AI);
    ADC_SetPin(HEATER_ISENSE_AI);
    ADC_SetPin(ECU_2_ISENSE_AI);
    ADC_SetPin(ECU_1_ISENSE_AI);
    ADC_SetPin(V12_MONITOR_AI);
    ADC_SetPin(BATT_ISENSE_AI);
    ADC_SetPin(DCDC_ISENSE_AI);
    ADC_SetPin(IC_CONTROLLER_ISENSE_AI);
    ADC_SetPin(RADIATOR_INPUT_TEMP_AI);
    ADC_SetPin(RADIATOR_OUTPUT_TEMP_AI);
    ADC_SetPin(P12_MONITOR_AI);
    ADC_SetPin(PILOT_MONITOR_AI);
    ADC_SetPin(PROXIMITY_MONITOR_AI);


    /*PWM*/
    pwmOCinit(PWM_1_OUT);
    pwmOCinit(PWM_2_OUT);

    /*UART*/
    Uart1INIT(UART_TX, UART_RX, UART_BAUD_115200, CLOCK_SystemFrequencyGet());
    /*CAN*/
    CAN_Init(CAN_TX, CAN_RX, CAN_BAUD_500k, CAN_DISABLE, CLOCK_SystemFrequencyGet());
    
    //set wakeup sources
    PINS_internalRegisters_SetInterrupt(IGNITION_SWITCH_IN, 1);
    /*CAN is wake source already in CAN_Init()*/

}

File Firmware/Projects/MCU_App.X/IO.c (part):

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static uint8_t MOTOR_CONTROLLER_fault = 0;
static uint8_t BMS_CONTROLLER_fault = 0;
static uint8_t SPARE_1_CONTROLLER_fault = 0;
static uint8_t BATT_fault = 0;
static uint8_t DCDC_fault = 0;
static uint8_t IC_CONTROLLER_fault = 0;

/*Current values*/
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}

void IO_SET_DEBUG_LED_EN(uint8_t state) {
    PINS_write(DEBUG_LED_EN, state);
}

void IO_SET_DEBUG_PIN_EN(uint8_t state) {
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
void IO_SET_BMS_CONTROLLER_EN(uint8_t state) {
    if (BMS_CONTROLLER_fault == 0) {
        PINS_write(BMS_CONTROLLER_EN, state);
    }
}

void IO_SET_J1772_CONTROLLER_EN(uint8_t state) {
    PINS_write(J1772_CONTROLLER_EN, state);
}

void IO_SET_MOTOR_CONTROLLER_EN(uint8_t state) {
    if (MOTOR_CONTROLLER_fault == 0) {
        PINS_write(MOTOR_CONTROLLER_EN, state);
    }
}

void IO_SET_CHARGE_CONTROLLER_EN(uint8_t state) {
    if (CHARGE_CONTROLLER_fault == 0) {
        PINS_write(CHARGE_CONTROLLER_EN, state);
    }
}

void IO_SET_PILOT_EN(uint8_t state) {
    PINS_write(PILOT_EN, state);
}

void IO_SET_BRAKE_LIGHT_EN(uint8_t state) {
    if (BRAKELIGHT_fault == 0) {
        PINS_write(BRAKE_LIGHT_EN, state);
    }
}

void IO_SET_TAILLIGHT_EN(uint8_t state) {
    if (TAILLIGHT_fault == 0) {
        PINS_write(TAILLIGHT_EN, state);
    }
}

void IO_SET_HEADLIGHT_HI_EN(uint8_t state) {
    if (HIGHBEAM_fault == 0) {
        PINS_write(HEADLIGHT_HI_EN, state);
    }
}

void IO_SET_HEADLIGHT_LO_EN(uint8_t state) {
    if (LOWBEAM_fault == 0) {
        PINS_write(HEADLIGHT_LO_EN, state);
    }
}

void IO_SET_CHARGER_CONTACTOR_EN(uint8_t state) {
    PINS_write(CHARGER_CONTACTOR_EN, state);
}

void IO_SET_DCDC_CONTACTOR_EN(uint8_t state) {
    PINS_write(DCDC_CONTACTOR_EN, state);
}

void IO_SET_BATTERY_CONTACTOR_EN(uint8_t state) {
    PINS_write(BATTERY_CONTACTOR_EN, state);
}

void IO_SET_PRECHARGE_RELAY_EN(uint8_t state) {
    PINS_write(PRECHARGE_RELAY_EN, state);
}

void IO_SET_HORN_EN(uint8_t state) {
    if (HORN_fault == 0) {
        PINS_write(HORN_EN, state);
    }
}

void IO_SET_AUX_PORT_EN(uint8_t state) {
    if (AUX_PORT_fault == 0) {
        PINS_write(AUX_PORT_EN, state);
    }
}

void IO_SET_TURN_SIGNAL_FR_EN(uint8_t state) {
    PINS_write(TURN_SIGNAL_FR_EN, state);
}

void IO_SET_TURN_SIGNAL_RR_EN(uint8_t state) {
    PINS_write(TURN_SIGNAL_RR_EN, state);
}

void IO_SET_TURN_SIGNAL_FL_EN(uint8_t state) {
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}

void IO_SET_TURN_SIGNAL_RL_EN(uint8_t state) {
    PINS_write(TURN_SIGNAL_RL_EN, state);
}

void IO_SET_HEATED_GRIPS_EN(uint8_t state) {
    if (HEATED_GRIPS_fault == 0) {
        PINS_write(HEATED_GRIPS_EN, state);
    }
}

void IO_SET_HEATED_SEAT_EN(uint8_t state) {
    if (HEATED_SEAT_fault == 0) {
        PINS_write(HEATED_SEAT_EN, state);
    }
}

void IO_SET_SW_EN(uint8_t state) {
    PINS_write(SW_EN, state);
}

void IO_SET_DIAG_EN(uint8_t state) {
    PINS_write(DIAG_EN, state);
}

void IO_SET_DIAG_SELECT_EN(uint8_t state) {
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
void IO_SET_DCDC_EN(uint8_t state) {
    //if (DCDC_fault == 0) {
        PINS_write(DCDC_EN, state);
    //}
}

void IO_SET_BATT_EN(uint8_t state) {
    //if (BATT_fault == 0) {
        PINS_write(BATT_EN, state);
    //}
}

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
void IO_SET_PUMP_1_EN(uint8_t state) {
    if (PUMP_fault == 0) {
        PINS_write(PUMP_1_EN, state);
    }
}

void IO_SET_FAN_1_EN(uint8_t state) {
    if (FAN_fault == 0) {
        PINS_write(FAN_1_EN, state);
    }
}

/*INPUTS*/

uint8_t IO_GET_DEBUG_LED_EN(void) {
    return PINS_read(DEBUG_LED_EN);
}

uint8_t IO_GET_DEBUG_PIN_EN(void) {
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}

uint8_t IO_GET_BMS_CONTROLLER_EN(void) {
    return PINS_read(BMS_CONTROLLER_EN);
}

uint8_t IO_GET_J1772_CONTROLLER_EN(void) {
    return PINS_read(J1772_CONTROLLER_EN);
}

uint8_t IO_GET_MOTOR_CONTROLLER_EN(void) {
    return PINS_read(MOTOR_CONTROLLER_EN);
}

uint8_t IO_GET_CHARGE_CONTROLLER_EN(void) {
    return PINS_read(CHARGE_CONTROLLER_EN);
}

uint8_t IO_GET_PILOT_EN(void) {
    return PINS_read(PILOT_EN);
}

uint8_t IO_GET_BRAKE_LIGHT_EN(void) {
    return PINS_read(BRAKE_LIGHT_EN);
}

uint8_t IO_GET_TAILLIGHT_EN(void) {
    return PINS_read(TAILLIGHT_EN);
}

uint8_t IO_GET_HEADLIGHT_HI_EN(void) {
    return PINS_read(HEADLIGHT_HI_EN);
}

uint8_t IO_GET_HEADLIGHT_LO_EN(void) {
    return PINS_read(HEADLIGHT_LO_EN);
}

uint8_t IO_GET_CHARGER_CONTACTOR_EN(void) {
    return PINS_read(CHARGER_CONTACTOR_EN);
}

uint8_t IO_GET_DCDC_CONTACTOR_EN(void) {
    return PINS_read(DCDC_CONTACTOR_EN);
}

uint8_t IO_GET_BATTERY_CONTACTOR_EN(void) {
    return PINS_read(BATTERY_CONTACTOR_EN);
}

uint8_t IO_GET_PRECHARGE_RELAY_EN(void) {
    return PINS_read(PRECHARGE_RELAY_EN);
}

uint8_t IO_GET_HORN_EN(void) {
    return PINS_read(HORN_EN);
}

uint8_t IO_GET_AUX_PORT_EN(void) {
    return PINS_read(AUX_PORT_EN);
}

uint8_t IO_GET_TURN_SIGNAL_FR_EN(void) {
    return PINS_read(TURN_SIGNAL_FR_EN);
}

uint8_t IO_GET_TURN_SIGNAL_RR_EN(void) {
    return PINS_read(TURN_SIGNAL_RR_EN);
}

uint8_t IO_GET_TURN_SIGNAL_FL_EN(void) {
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}

uint8_t IO_GET_TURN_SIGNAL_RL_EN(void) {
    return PINS_read(TURN_SIGNAL_RL_EN);
}

uint8_t IO_GET_HEATED_GRIPS_EN(void) {
    return PINS_read(HEATED_GRIPS_EN);
}

uint8_t IO_GET_HEATED_SEAT_EN(void) {
    return PINS_read(HEATED_SEAT_EN);
}

uint8_t IO_GET_SW_EN(void) {
    return PINS_read(SW_EN);
}

uint8_t IO_GET_DIAG_EN(void) {
    return PINS_read(DIAG_EN);
}

uint8_t IO_GET_DIAG_SELECT_EN(void) {
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}

uint8_t IO_GET_DCDC_EN(void) {
    return PINS_read(DCDC_EN);
}

uint8_t IO_GET_BATT_EN(void) {
    return PINS_read(BATT_EN);
}

uint8_t IO_GET_CAN_SLEEP_EN(void) {
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}

uint8_t IO_GET_PUMP_1_EN(void) {
    return PINS_read(PUMP_1_EN);
}

uint8_t IO_GET_FAN_1_EN(void) {
    return PINS_read(FAN_1_EN);
}

uint8_t IO_GET_IC_CONTROLLER_FAULT(void) {
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}

uint8_t IO_GET_TURN_SIGNAL_L_STATUS(void) {
    return PINS_read(TURN_SIGNAL_L_STATUS);
}

uint8_t IO_GET_TURN_SIGNAL_R_STATUS(void) {
    return PINS_read(TURN_SIGNAL_R_STATUS);
}

uint8_t IO_GET_CONTACT_1_2_STATUS(void) {
    return PINS_read(CONTACT_1_2_STATUS);
}

uint8_t IO_GET_CONTACT_3_4_STATUS(void) {
    return PINS_read(CONTACT_3_4_STATUS);
}

uint8_t IO_GET_SPARE_SWITCH_1_IN(void) {
    return PINS_read(SPARE_SWITCH_1_IN) ? 0 : 1;
}

uint8_t IO_GET_SPARE_SWITCH_2_IN(void) {
    return PINS_read(SPARE_SWITCH_2_IN) ? 0 : 1;
}

uint8_t IO_GET_BRAKE_SWITCH_1_IN(void) {
    return PINS_read(BRAKE_SWITCH_1_IN) ? 0 : 1;
}

uint8_t IO_GET_BRAKE_SWITCH_2_IN(void) {
    return PINS_read(BRAKE_SWITCH_2_IN) ? 0 : 1;
}

uint8_t IO_GET_IGNITION_SWITCH_IN(void) {
    return PINS_read(IGNITION_SWITCH_IN) ? 0 : 1;
}

uint8_t IO_GET_KILL_SWITCH_IN(void) {
    return PINS_read(KILL_SWITCH_IN) ? 1 : 0;
}

uint8_t IO_GET_TURN_LEFT_SWITCH_IN(void) {
    return PINS_read(TURN_LEFT_SWITCH_IN) ? 0 : 1;
}

uint8_t IO_GET_TURN_RIGHT_SWITCH_IN(void) {
    return PINS_read(TURN_RIGHT_SWITCH_IN) ? 0 : 1;
}

uint8_t IO_GET_BRIGHTS_SWITCH_IN(void) {
    return PINS_read(BRIGHTS_SWITCH_IN) ? 0 : 1;
}

uint8_t IO_GET_HORN_SWITCH_IN(void) {
    return PINS_read(HORN_SWITCH_IN) ? 0 : 1;
}

uint8_t IO_GET_KICKSTAND_SWITCH_IN(void) {
    return PINS_read(KICKSTAND_SWITCH_IN) ? 0 : 1;
}

/*ANALOG*/
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
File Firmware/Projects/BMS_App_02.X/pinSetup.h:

/* 
 * File:   pinSetup.h
 * Author: kid group
 *
 * Created on March 1, 2018, 8:04 AM
 */

#ifndef PINSETUP_H
#define	PINSETUP_H

#include <stdint.h>
#include "pins.h"

/*DIGITAL INPUTS AND OUTPUTS*/

//Outputs
#define SW_EN PIN_DEF(B,4)
#define DCDC_EN PIN_DEF(B,7)
#define EV_CHARGER_EN PIN_DEF(B,8)
#define PRE_CHARGE_EN PIN_DEF(B,12)
#define DEBUG_PIN PIN_DEF(B,14)
#define DEBUG_LED_EN PIN_DEF(C,5)
#define PILOT_EN PIN_DEF(C,6)
#define MUX_A PIN_DEF(E,15)
#define MUX_B PIN_DEF(C,10)
#define MUX_C PIN_DEF(C,13)
#define CAN_TX_PIN PIN_DEF(G,6)

//Inputs
#define V5_SW_nFAULT PIN_DEF(A,8)
#define V12_POWER_STATUS PIN_DEF(D,8)
#define DCDC_nFAULT PIN_DEF(D,6)
#define EV_CHARGER_nFAULT PIN_DEF(D,5)

/*ANALOG*/
#define ISOLATION_VOLTAGE_AI AN0
#define HV_BUS_VOLTAGE_AI AN1
#define EV_CHARGER_CURRENT_AI AN2
#define DCDC_OUTPUT_CURRENT_AI AN3
#define EV_CHARGER_VOLTAGE_AI AN4
#define DCDC_OUTPUT_VOLTAGE_AI AN5
#define HIGH_CURRENT_SHUNT_AI AN6
#define PROMIXITY_MONINOTR_AI AN7
#define MUX_1_AI AN8
#define TRANSDUCER_INPUT_AI AN9
#define LOW_CURRENT_SHUNT_AI AN10
#define MUX_2_AI AN11
#define MUX_3_AI AN12
#define PILOT_MONITOR_AI AN13
#define VBUS_VOLTAGE_AI AN14


/*PWM*/
#define CONTACTOR_1_PWM PWM_PIN_RP57
#define CONTACTOR_2_PWM PWM_PIN_RP56

/*COMUNICATION*/
//Uart
#define UART_TX RP97_OUT
#define UART_RX RPI96_IN

//CAN
#define CAN_TX RP118_OUT
#define CAN_RX RPI119_IN

//SPI
#define SPI_CS PIN_DEF(C,4)


/**
 * @PinSetup_Init will initialize all pins for their intended usage as defined above
 */
void PinSetup_Init(void);


#endif	/* PINSETUP_H */
